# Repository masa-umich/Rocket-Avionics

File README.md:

# Rocket-Avionics
Embedded firmware for Rocket Avionics

Read Me last updated: 9/2/2025

## Note:
This is a mono-repo meaning that code for the bay boards, flight computer, and all other rocket avionics should go into sub-directories of this repo. The only exception to this is Limewire since that is an interface to the flight computer and not part of rocket avionics itself.

Find all firmware that actually runs on boards in `stm-flight-sw/`

Find all the templates in `stm-templates/`

Sensor Emulation Board (SEB) -> `SEB/`

Apogee Detection Sims & RTOS Threads -> `apogee-detection/`

All on-board driver firmware -> `board-drivers/`

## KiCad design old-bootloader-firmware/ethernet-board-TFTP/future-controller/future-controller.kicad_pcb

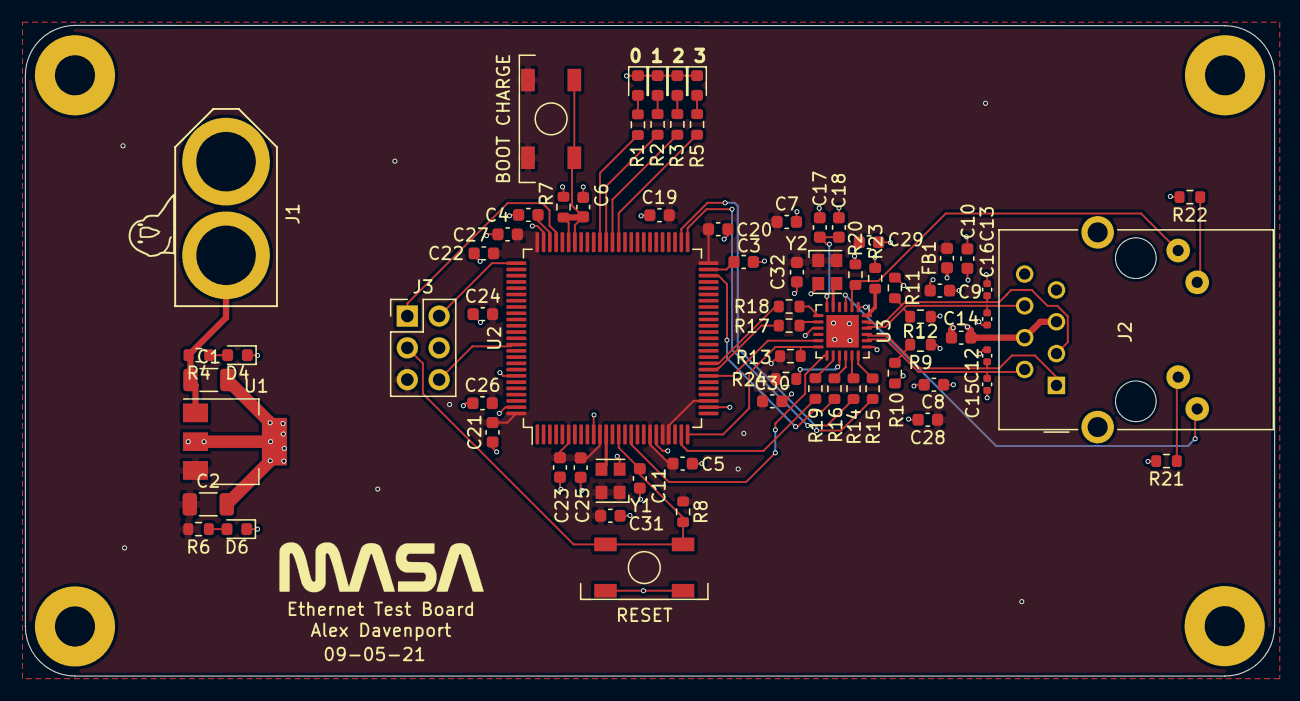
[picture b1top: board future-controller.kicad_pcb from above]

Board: 4 copper layers, 99.8 x 52.0 mm, 77 parts (0 on the bottom side), 49 nets.

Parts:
BOOT CHARGE: SW_SPST; SKQGADE010
C1, C2: 10uF; C_1206_3216Metric
C3, C4: 2.2uF; C_0603_1608Metric
C5, C7, C8, C9, C11, C19, C20, C21, C22, C23, C24, C31, C32: 100nF; C_0603_1608Metric
C6, C25, C26, C27, C29, C30: 10uF; C_0603_1608Metric
C10: 4.7uF; C_0603_1608Metric
C12, C13, C15, C16: 10pF; C_0402_1005Metric
C14: 0.022uF; C_0603_1608Metric
C17: 1uF; C_0603_1608Metric
C18: 470pF; C_0603_1608Metric
C28: 100nf; C_0603_1608Metric
D1, D2, D3, D4, D5, D6: LED; LED_0603_1608Metric
FB1: FB; C_0603_1608Metric
J1: XT-60_female; XT-60
J2: RJ45_Amphenol_RJMG1BD3B8K1ANR; RJ45_Amphenol_RJMG1BD3B8K1ANR_modified
J3: Debug Header; PinHeader_2x03_P2.54mm_Vertical
MH1, MH2, MH3, MH4: MountingHole; MountingHole_3.2mm_M3_Pad
R1, R2, R3, R5: 220; R_0603_1608Metric
R4, R7, R8, R20, R24: 10k; R_0603_1608Metric
R6: 1k; R_0603_1608Metric
R9, R10, R11, R12: 49.9; R_0603_1608Metric
R13: 1k5; R_0603_1608Metric
R14, R15, R16, R17, R18, R19: 33; R_0603_1608Metric
R21, R22: 270; R_0603_1608Metric
R23: 12k1; R_0603_1608Metric
RESET: SW_SPST; SKQGADE010
U1: TL1963A-33DCYR; SOT-223
U2: STM32F427VGTx; LQFP-100_14x14mm_P0.5mm
U3: LAN8742A; QFN-24-1EP_4x4mm_P0.5mm_EP2.6x2.6mm
Y1: ECS-TXO-2520MV-500; Oscillator_SMD_Kyocera_KC2520Z-4Pin_2.5x2.0mm
Y2: ECS-TXO-2520MV-250; Oscillator_SMD_Kyocera_KC2520Z-4Pin_2.5x2.0mm

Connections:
+3V3: BOOT CHARGE.1, C2.1, C5.1, C7.1, C19.2, C20.2, C21.2, C22.2, C23.2, C24.2, C25.2, C26.2, C27.2, C28.1, C29.1, C30.1, C31.1, C32.1, FB1.2, J3.5, R6.2, R8.1, R13.1, R24.2, U1.3, U2.6, U2.11, U2.19, U2.21, U2.22, U2.28, U2.50, U2.75, U2.100, U3.9, Y1.1, Y1.4, Y2.1, Y2.4
+12V: C1.1, J1.1, R4.2, U1.1
/25MHZ_CLK: U3.5, Y2.3
/50MHZ_CLK: U2.12, Y1.3
/LED1: J2.L4, U3.3
/LED2: J2.L1, R20.1, U3.2
/RX_N: C16.1, J2.R6, R12.2, U3.22
/RX_P: C13.1, J2.R3, R11.2, U3.23
/TX_N: C15.1, J2.R2, R10.2, U3.20
/TX_P: C12.1, J2.R1, R9.2, U3.21
/VDDA: C8.1, C9.1, C10.1, C14.1, FB1.1, J2.R4, J2.R5, R9.1, R10.1, R11.1, R12.1, U3.1, U3.19
BOOT_CHARGE: BOOT CHARGE.2, C6.1, R7.1, U2.69, U2.70
CRS_DV: U2.32, U3.11
GND: C1.2, C2.2, C3.2, C4.2, C5.2, C6.2, C7.2, C8.2, C9.2, C10.2, C11.1, C12.2, C13.2, C14.2, C15.2, C16.2, C17.2, C18.2, C19.1, C20.1, C21.1, C22.1, C23.1, C24.1, C25.1, C26.1, C27.1, C28.2, C29.2, C30.2, C31.2, C32.2, D1.1, D2.1, D3.1, D4.1, D5.1, D6.1, J1.2, J2.13, J2.R8, J3.4, MH1.1, MH2.1, MH3.1, MH4.1, R7.2, R20.2, R21.2, R22.2, R23.2, RESET.1, U1.2, U1.4, U2.10, U2.20, U2.27, U2.74, U2.94, U2.99, U3.25, Y1.2, Y2.2
LED0_gpio: R1.2, U2.65
LED1_gpio: R2.2, U2.64
LED2_gpio: R3.2, U2.63
LED3_gpio: R5.2, U2.62
MDC: U2.16, U3.13
MDIO: R13.2, U2.25, U3.12
NRST: C11.2, J3.3, R8.2, RESET.2, U2.14
unnamed: C3.1, U2.49
unnamed: C4.1, U2.73
unnamed: C17.1, C18.1, U3.6
unnamed: D1.2, R1.1
unnamed: D2.2, R2.1
unnamed: D3.2, R3.1
unnamed: D4.2, R4.1
unnamed: D5.2, R5.1
unnamed: D6.2, R6.1
unnamed: J2.L2, R22.1
unnamed: J2.L3, R21.1
unnamed: R14.1, U3.17
unnamed: R15.1, U3.18
unnamed: R16.1, U3.16
unnamed: R17.1, U3.8
unnamed: R18.1, U3.7
unnamed: R19.1, U3.14
unnamed: R23.1, U3.24
unnamed: R24.1, U3.15
REFCLK: R19.2, U2.24
RXD0: R17.2, U2.33
RXD1: R18.2, U2.34
SWCLK: J3.2, U2.76
SWDIO: J3.1, U2.72
SWO: J3.6, U2.89
TXD0: R14.2, U2.51
TXD1: R15.2, U2.52
TXEN: R16.2, U2.48

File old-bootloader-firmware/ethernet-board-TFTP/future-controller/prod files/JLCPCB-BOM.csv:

Comment,Designator,Footprint,JLCPCB Part Number
4.7uF,C10,603,C19666
0.022uF,C14,603,C21122
1uF,C17,603,C15849
470pF,C18,603,C1620
10uF,"C1,C2",1206,C13585
2.2uF,"C3,C4",603,C23630
10uF,"C6,C25,C26,C27,C29,C30",603,C19702
100nF,"C5,C7,C8,C9,C11,C19,C20,C21,C22,C23,C24,C28,C31,C32",603,C14663
LED,"D1,D2,D3,D4,D5,D6",603,C138543
FB,FB1,603,C85831
220,"R1,R2,R3,R5",603,C22962
1k5,R13,603,C22843
33,"R14,R15,R16,R17,R18,R19",603,C23140
270,"R21,R22",603,C22966
12k1,R23,603,C22864
1k,R6,603,C21190
10k,"R4,R7,R8,R20,R24",603,C25804
49.9,"R9,R10,R11,R12",603,C23185
SKQGADE010,"SW1,SW2",SW-SMD,C116647
TL1963A-33DCYR,U1,SOT-223,C181262
STM32F427VGTx,U2,LQFP-100_14.0x14.0x0.5P,C91929
LAN8742A,U3,QFN-24_EP_4.0x4.0x0.5P,C153279

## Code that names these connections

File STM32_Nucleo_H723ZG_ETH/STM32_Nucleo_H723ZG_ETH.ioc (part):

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Mcu.Name=STM32H723ZGTx
Mcu.Package=LQFP144
Mcu.UserName=STM32H723ZGTx
PA1.GPIOParameters=GPIO_Speed,GPIO_Label
PA1.GPIO_Label=RMII_REF_CLK
PA1.GPIO_Speed=GPIO_SPEED_FREQ_VERY_HIGH
PA1.Mode=RMII
PA1.Signal=ETH_REF_CLK
PA10.GPIOParameters=GPIO_Label
PA10.GPIO_Label=USB_FS_ID
PA10.Signal=USB_OTG_HS_ID
PA13(JTMS/SWDIO).GPIOParameters=GPIO_Label
PA13(JTMS/SWDIO).GPIO_Label=SWDIO
PA13(JTMS/SWDIO).Signal=DEBUG_JTMS-SWDIO
PA14(JTCK/SWCLK).GPIOParameters=GPIO_Label
PA14(JTCK/SWCLK).GPIO_Label=SWCLK
PA14(JTCK/SWCLK).Signal=DEBUG_JTCK-SWCLK
PA2.GPIOParameters=GPIO_Speed,GPIO_Label
PA2.GPIO_Label=RMII_MDIO
PA2.GPIO_Speed=GPIO_SPEED_FREQ_VERY_HIGH
PA2.Mode=RMII
PA2.Signal=ETH_MDIO
PA7.GPIOParameters=GPIO_Speed,GPIO_Label
PA7.GPIO_Label=RMII_CRS_DV
PA7.GPIO_Speed=GPIO_SPEED_FREQ_VERY_HIGH
PA7.Mode=RMII
PA7.Signal=ETH_CRS_DV
PA9.GPIOParameters=GPIO_Label
PA9.GPIO_Label=USB_FS_VBUS
PA9.Signal=USB_OTG_HS_VBUS
PB0.GPIOParameters=GPIO_Label
PB0.GPIO_Label=LED1
PB0.Signal=GPIO_Output
PB13.GPIOParameters=GPIO_Speed,GPIO_Label
PB13.GPIO_Label=RMII_TXD1
PB13.GPIO_Speed=GPIO_SPEED_FREQ_VERY_HIGH
PB13.Mode=RMII
PB13.Signal=ETH_TXD1
PB14.GPIOParameters=GPIO_Label
PB14.GPIO_Label=LED2
PB14.Signal=GPIO_Output
PB3(JTDO/TRACESWO).GPIOParameters=GPIO_Label
PB3(JTDO/TRACESWO).GPIO_Label=SWO
PB3(JTDO/TRACESWO).Signal=DEBUG_JTDO-SWO
PC1.GPIOParameters=GPIO_Speed,GPIO_Label
PC1.GPIO_Label=RMII_MDC
PC1.GPIO_Speed=GPIO_SPEED_FREQ_VERY_HIGH
PC1.Mode=RMII
PC1.Signal=ETH_MDC
PC13.GPIOParameters=GPIO_Label
PC13.GPIO_Label=B1 (Blue_User_Button)
PC13.Signal=GPIO_Input
PC14-OSC32_IN.Signal=RCC_OSC32_IN
PC15-OSC32_OUT.Signal=RCC_OSC32_OUT
PC4.GPIOParameters=GPIO_Speed,GPIO_Label
PC4.GPIO_Label=RMII_RXD0
PC4.GPIO_Speed=GPIO_SPEED_FREQ_VERY_HIGH
PC4.Mode=RMII
PC4.Signal=ETH_RXD0
PC5.GPIOParameters=GPIO_Speed,GPIO_Label
PC5.GPIO_Label=RMII_RXD1
PC5.GPIO_Speed=GPIO_SPEED_FREQ_VERY_HIGH
PC5.Mode=RMII
PC5.Signal=ETH_RXD1
PD10.GPIOParameters=GPIO_Label
PD10.GPIO_Label=USB_FS_PWR_EN
PD10.Signal=GPIO_Output
PD8.GPIOParameters=GPIO_Label
PD8.GPIO_Label=STLK_VCP_RX
PD8.Signal=USART3_TX
PD9.GPIOParameters=GPIO_Label
PD9.GPIO_Label=STLK_VCP_TX
PD9.Signal=USART3_RX
PE1.GPIOParameters=GPIO_Label
PE1.GPIO_Label=LED0
PE1.Signal=GPIO_Output
PG11.GPIOParameters=GPIO_Speed,GPIO_Label
PG11.GPIO_Label=RMII_TX_EN
PG11.GPIO_Speed=GPIO_SPEED_FREQ_VERY_HIGH
PG11.Mode=RMII
PG11.Signal=ETH_TX_EN
PG13.GPIOParameters=GPIO_Speed,GPIO_Label
PG13.GPIO_Label=RMII_TXD0
PG13.GPIO_Speed=GPIO_SPEED_FREQ_VERY_HIGH
PG13.Mode=RMII
PG13.Signal=ETH_TXD0
PG7.GPIOParameters=GPIO_Label
PG7.GPIO_Label=USB_FS_OVCR
PG7.Signal=GPXTI7
PH0-OSC_IN.GPIOParameters=GPIO_Label
PH0-OSC_IN.GPIO_Label=MCO
PH0-OSC_IN.Signal=RCC_OSC_IN
PH1-OSC_OUT.Signal=RCC_OSC_OUT
RCC.HSE_VALUE=8000000
RCC.SYSCLKFreq_VALUE=500000000
RCC.SYSCLKSource=RCC_SYSCLKSOURCE_PLLCLK
board=NUCLEO-H723ZG
boardIOC=true

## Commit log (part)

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2023-11-06 Include old flash code and added individual readme
2023-11-07 Added files, ethernet and GPS chip
2023-11-08 Starting ADC code
2023-11-12 haha dma sucks
2023-11-14 Apparently there is no simple DMA interrupt
2023-12-02 preliminary implementation of GPS driver
2024-01-21 Finished Driver :)
2024-01-23 Add IMU initialization and communication functions
2024-01-23 Temperature function test - not sure if the conversion is right
2024-01-26 Done pending testing
2024-02-02 Update IMU configuration and conversion functions
2024-02-09 Added conditional HAL library checks, polished comments. Pending proper testing.
2024-02-09 oops can't scan for a file that you haven't defined yet... using #include "main.h" does the hal inclusion for us
2024-02-09 weird register behavior again yaaaay
2024-02-16 Add Ethernet driver and initial documentation
2024-02-18 Uh idk
2024-02-18 Added Example code for Barometer
2024-02-22 Cleaned up and renamed files
2024-03-09 Changed HAL include to main.h include for better compat
2024-03-11 Started work on new packet parser
2024-03-22 i love you
2024-03-24 Updated header files names to hopefully fix build errors
2024-03-27 Changed packet parser to new implementation
2024-03-27 Refactor flash chip initialization and function calls
2024-04-08 Setup STM Project
2024-04-21 I2C IMU Port
2024-04-22 Integrated Flash + Python decoder
2024-04-28 Made code more, and less, dumb
2024-09-06 The great avionics code consolidation
2024-09-26 progress on FC template
2024-10-08 lwip+freertos
2024-10-13 more eth progress
2024-10-20 add boilerplate for ADS1120
2024-10-20 update drivers README with correct ADS1120 SPI Bus
2024-10-21 lonely-m
2024-10-21 update documentation
2024-10-21 test
2025-01-09 Thermocouple driver progress
2025-01-12 Secondary Barometer Boilerplate
2025-01-12 more barometer setup
2025-01-12 Added write, read, reset
2025-01-13 Limestone template update
2025-01-13 Reorganized some things
2025-01-13 more basic functions
2025-01-14 more MS5611 stuff
2025-01-18 Create temp
2025-01-18 prints out height data at regular intervals
2025-01-19 added SEB
2025-01-19 add open load detection to flight computer
2025-01-19 untested conversion
2025-01-20 Added getAlt
2025-01-26 Updated Valve driver and MS5611
2025-01-26 MS5611 Debug Pt1
2025-01-26 Changed file name of height data to match program input
2025-02-09 switched to C++
2025-02-09 Kalman filter skeleton
    This code first initializes the noise covariance matrix for all the three sensors fused together (barometer, IMU, GPS) based on their spec sheets and then do the standard Kalman filter steps. However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
2025-02-10 Update Kalman_rocket_apogee.cpp
    This code first initializes the noise covariance matrix for all the three sensors (barometer, IMU, GPS) based on their spec sheets and then do the standard Kalman filter steps to fuse them together. 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
2025-02-11 ADS1120 driver progress/switch to async structure
2025-02-16 Added TCP messaging struct
2025-02-16 finish ms5611 :) !!!
2025-02-17 Start new TCP server
2025-03-02 Add dev board pinout to M24256E README.md
2025-03-07 mostly working AD simulation; just a little bit late (2.5 s post-apogee)
2025-03-09 fixed integer division error in std::accumulate, also downsized arrays
2025-03-16 Updated limestone template with new pins
2025-03-16 Add TCP message serialization/deserialization tests
2025-03-22 Add new version of M24256E drivers
2025-03-29 Move EEPROM #defines from header to source
2025-04-03 Fix some documentation in M24256E.h
2025-04-06 Added documentation + apogee-task.c / .h
2025-04-11 bug fixes
2025-04-12 done?
2025-04-13 simulator start
2025-04-13 mmm beautiful documentation
2025-04-13 Added example to documentation
2025-04-13 cleanup code
2025-04-18 clean up
2025-04-21 Added SPI setup to TC driver documentation
2025-04-27 Include only main.h in EEPROM driver
2025-04-27 Implement rest of read functions for EEPROM driver
2025-05-01 Update TCP message protocol
    I have not yet added the single bit at the beginning for encoding message length.
2025-05-01 Store actual contents instead of shifted contents of CDA
2025-05-01 Fix num_data_bytes_to_write calculation
2025-05-01 Fix error checking for invalid addresses
2025-05-01 Add max number of write attempts to EEPROM polling write
2025-05-01 Add initial implementation of eeprom_is_id_page_locked
2025-06-02 Redid a lot of SEB but still not working
2025-06-02 TCP Server major progress!
2025-07-04 Set up RTC and NTP using LWIP's SNTP client
2025-07-04 Added gitignore to limestone-firmware
2025-07-06 Updated IMU driver to support multiple addresses and added current sensing and PT math to limestone-firmware
2025-07-06 Fixed type issues with RTC and got the time synchronization down to under 1ms
2025-07-11 THE FLIGHT COMPUTER COMMUNICATES WITH LIMEWIRE!!
2025-07-12 added option for baro or MECO+baro detection for sims
2025-07-14 EEPROM config implemented + remote EEPROM writing over TFTP
2025-07-14 Added the rest of the rocket state and telemetry parsing. At this point the telemetry for the entire rocket can be held in memory, and parsed from LMP
2025-07-17 Telemetry task done, packet handler almost done.
2025-07-19 Flash and UDP logging of error messages done. Also fixed a timing issue with the MS5611 driver.
2025-07-29 TCP server error handling started - listening thread done
2025-07-30 TCP server errno handling done
2025-08-02 TCP server error handling and logging done!
2025-08-06 post-apogee logic added (drogue and main chute deployment)
2025-08-08 Startup error handling and logging done
2025-08-10 added speed_LUT to help with post-MECO timeout
2025-08-11 Fixed a stupid problem
2025-08-15 TCP client mostly done + a couple bug fixes
2025-08-16 TCP client done, bay board firmware 50% ported
2025-08-18 flight summary written to .txt file after program execution
2025-08-18 remove unused include
2025-08-22 more major changes to apogee_task, not done yet
2025-08-23 still more changes to apogee_task, addressing unit inconsistencies next
2025-09-01 very minor update
2025-09-02 Reorg :)
2025-09-21 Comment out unnecessary IMU class.
    IMU class in noise_generator.hpp was preventing compilation because
    of unused variables. Not needed currently, so commented out.
2025-09-21 feat(sx1280): initialize new FreeRTOS-compliant driver structure
    Replaces the entire previous driver structure with a new structure.
    designed to meet the requirements outlined in the Radio Firmware Project Spec:
    - clean, high-level API
    - thread-safe SPI wrapper using FreeRTOS critical sections.
2025-09-22 Major board comms fixes
2025-09-26 Add SX1280 command opcodes, expanded API
    Defined SX1280 command opcodes in the header for clarity and expanded the public API in SX1280.h
2025-09-30 IRQ based SEB
2025-10-01 SEB without HAL API
2025-10-03 Got MISO working on SEB
2025-10-08 Finishing up functions
    This is finishing up most functions as well as adding in other missing function prototypes (most to be reviewed).
2025-10-19 Fixes to typos in functions
    Fixing typos that was creating compilation errors
2025-10-26 added driver
2025-10-26 Fixes to comments
    Fixes to informal comments
2025-10-26 Made directory and LED blinking in state 0
2025-10-28 Update SX1280.c
    Replace HAL_Delay with vTaskDelay for RTOS compatibility
2025-10-28 wrote basic state machine
2025-10-28 Update SX1280.c
    Fix to setting Tx params
2025-10-29 Reorganize limestone firmware progress
2025-11-01 New sx1280 driver datasheet
2025-11-01 Update to drivers
    This is an update to the drivers accounting for the new SX1280 datasheet revision.
2025-11-04 rewrote state machine using switch statements
2025-11-09 Bay Board firmware refactoring done
2025-11-10 Added makefile versioning
2025-11-11 Work on versioning
2025-11-11 minor update to SX1280 firmware
    This is just minor fixes to the comments in the driver code, as well as further testing of the hardware.
2025-11-13 Testing versioning scripts on windows
2025-11-13 Logging delayed until after PHY initialization
2025-11-14 Converted versioning to a shell script, progress on LMP device command ACKs
2025-11-16 additional
2025-11-17 Changed log message index
2025-11-17 Add build info device command
2025-11-17 Added board temp telemetry channel
2025-11-18 Updates to radio driver and main.c
    These are big updates to how we transmit, test code for main.c, and reformatting.
2025-11-30 Keeping FC and BB firmware in sync
2025-12-02 ground states work correctly, incorporating apogee detection
2025-12-02 incorporated apogee detection, need to debug
2025-12-08 Re-designed telemetry networking stack to UDP. Shakedown successful
2025-12-27 wrote filter
2025-12-29 added velocity and orientation buffer, need to implement and update timers
2026-01-03 Fixed an issue with error logging number codes
2026-01-07 Made ntp script better
2026-01-08 Bay Board ntp script too
2026-01-12 Fixed more UDP telemetry issues
2026-01-15 Allocate more stack for critical tasks
2026-01-17 Attempts to fix FC crashing. Saving before changing clock config.
2026-01-19 Shakedown 2, flash broken
2026-01-20 Fixed networking parameters
2026-01-25 Fixed most issues, flash still broken
2026-01-31 Flash driver fixed, 1st Coldflow
2026-02-12 LWIP config changes
2026-02-12 UDP telemetry changes
2026-02-12 Initial handoff design
2026-02-13 Memory progress - still unstable
2026-02-13 Added malloc hooks to make malloc and free thread safe
2026-02-14 Coldflow weekend 3 - firmware stable
2026-02-19 added timer logic & comments
2026-02-23 finished adding comments in autosequence-script
2026-02-23 second round of comments
2026-02-23 removed stupid questions
2026-02-27 removed previous lockout detection, bug fixes, and implementing new lockout detection. Need to implement function stubs.
2026-03-07 Handoff and interface mostly done
2026-03-10 testing autosequence
    Generated synthetic data, fixed a few typos in functions to make sure tests run properly. Not 100% sure whether synthetic data is completely correct and whether "edge cases" actually occur.
2026-03-10 hot fix
    removed comment
2026-03-12 small bug fixes, working on synthetic testing
2026-03-13 Fixed GPS init
2026-03-17 Add lonelym
2026-03-18 Fixed flash dumping
2026-03-19 Small temp fix on autosequence to let handoff be tested this weekend
2026-03-20 minor bug fixes in ad-functions, bug fix for quadr_curve_fit, reordering of lapse rate / chute deploy pressure & small variable type changes in autosequence-script, added flight states in flight-auto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
2026-03-21 GPS changes, lots of small fixes, coldflow ready flight-autosequence
2026-03-21 debug files added, several bug & code tweaks to autosequence-script, other minor changes
2026-04-10 Change ground station MAC address
2026-04-12 csv parser c
2026-04-12 added a few things here and there, need to see whether changing it from 50ms per to 20ms per breaks anything/anything needs to be changed as a result
2026-04-12 Revert "csv parser c"
    This reverts commit 06b7f978f1f1e780c379c360bba4158bb2e5a933.
2026-04-13 Cleanup project directories
2026-04-16 testing autosequence on lm3 data
2026-04-20 Flash driver fixes and autosequence boot parameters
2026-04-22 Initial flight recorder project
2026-04-23 Flight Recorder firmware written
2026-04-23 autosequence works for pf2 data as well
2026-04-24 LM4 changes and radio bitmask for fluctus
2026-04-24 Added fluctus interface for autosequence
2026-04-30 Changed FR logging to be enabled/disabled
2026-05-01 Changed autosequence return value
2026-05-01 removed alt_dtr
2026-05-01 added clear
2026-05-01 Include path
2026-05-01 Added disarmed state
2026-05-01 Merged autosequence state definitions
2026-05-02 added boot_param logic
2026-05-02 Small fixes
2026-05-03 Autosequence logging + Flight recorder log msg logging
2026-05-03 Merged
2026-05-03 Added fluctus override flag to eeprom
2026-05-03 hotfix
2026-05-06 Include protection
2026-05-06 comments and tests written
2026-05-07 Flight recorder fixes
2026-05-07 matlab testing works for nominal flight
2026-05-07 More logging
2026-05-07 Final testing on FC
